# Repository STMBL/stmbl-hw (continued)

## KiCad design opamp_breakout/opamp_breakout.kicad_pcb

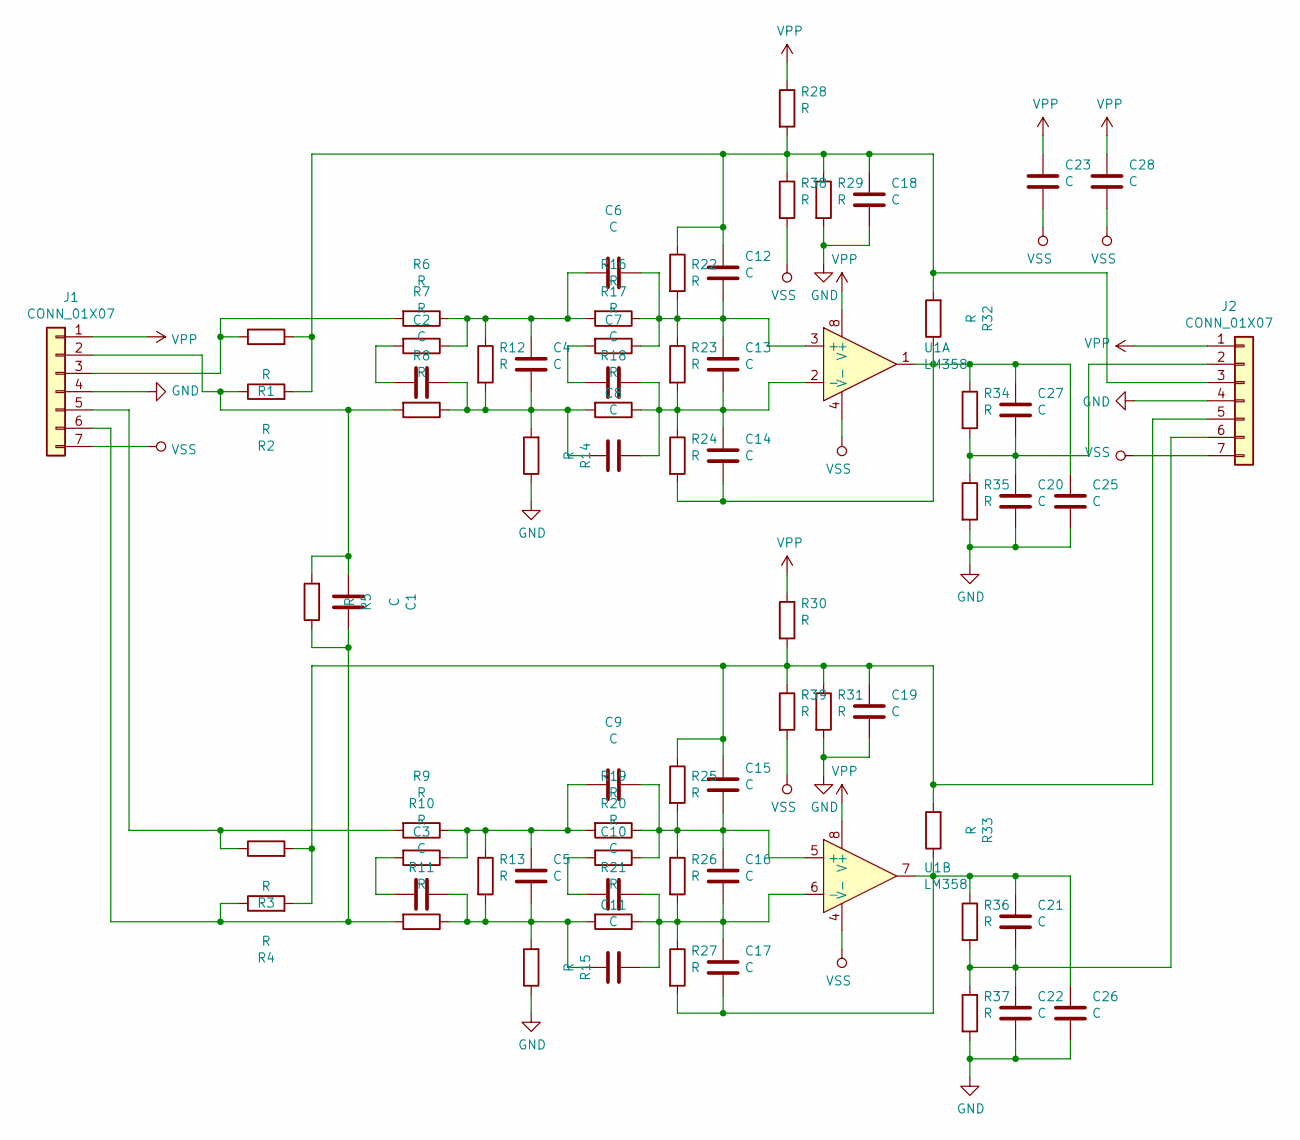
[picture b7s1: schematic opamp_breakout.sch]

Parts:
C1, C2, C3, C4, C5, C6, C7, C8, C9, C10, C11, C12, C13, C14, C15, C16, C17, C18, C19, C20, C21, C22, C23, C25, C26, C27, C28: C; 0603_jumper
J1, J2: CONN_01X07; Pin_Header_RM2.54_1x7_UP
R1, R2, R3, R4, R5, R6, R7, R8, R9, R10, R11, R12, R13, R14, R15, R16, R17, R18, R19, R20, R21, R22, R23, R24, R25, R26, R27, R28, R29, R30, R31, R32, R33, R34, R35, R36, R37, R38, R39: R; 0603_jumper
U1: LM358; SOIC-8-N

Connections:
GND: C18.2, C19.2, C20.2, C22.2, C25.2, C26.2, J1.4, J2.4, R14.1, R15.1, R29.2, R31.2, R35.2, R37.2
unnamed: C1.1, J1.6, R4.1, R5.1, R11.2
unnamed: C1.2, J1.2, R2.1, R5.2, R8.2
unnamed: C2.1, C4.2, C8.2, R8.1, R12.2, R14.2, R18.2
unnamed: C2.2, R7.2
unnamed: C3.2, R10.2
unnamed: C4.1, C6.2, R6.1, R7.1, R12.1, R16.2
unnamed: C5.1, C9.2, R9.1, R10.1, R13.1, R19.2
unnamed: C7.2, R17.2
unnamed: C10.1, C11.1, C16.2, C17.1, R21.1, R26.2, R27.1, U1.6 (-)
unnamed: C10.2, R20.2
unnamed: C3.1, C5.2, C11.2, R11.1, R13.2, R15.2, R21.2
unnamed: C12.1, C18.1, J2.3, R1.2, R2.2, R22.1, R28.2, R29.1, R32.2, R38.1
unnamed: C6.1, C12.2, C13.1, R16.1, R17.1, R22.2, R23.1, U1.3 (+)
unnamed: C7.1, C8.1, C13.2, C14.1, R18.1, R23.2, R24.1, U1.2 (-)
unnamed: C14.2, C25.1, C27.1, R24.2, R32.1, R34.1, U1.1
unnamed: C15.1, C19.1, J2.5, R3.2, R4.2, R25.1, R30.2, R31.1, R33.2, R39.1
unnamed: C9.1, C15.2, C16.1, R19.1, R20.1, R25.2, R26.1, U1.5 (+)
unnamed: C17.2, C21.1, C26.1, R27.2, R33.1, R36.1, U1.7
unnamed: C20.1, C27.2, J2.2, R34.2, R35.1
unnamed: C21.2, C22.1, J2.6, R36.2, R37.1
unnamed: J1.3, R1.1, R6.2
unnamed: J1.5, R3.1, R9.2
VPP: C23.1, C28.1, J1.1, J2.1, R28.1, R30.1, U1.8 (V+)
VSS: C23.2, C28.2, J1.7, J2.7, R38.2, R39.2, U1.4 (V-)

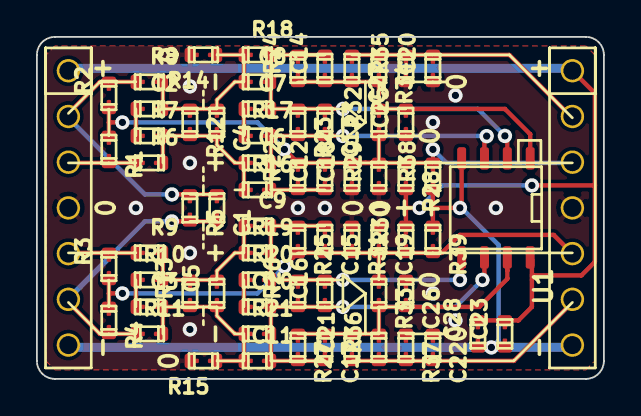
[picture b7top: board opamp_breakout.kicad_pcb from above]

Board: 2 copper layers, 31.5 x 19.0 mm, 69 parts (0 on the bottom side), 25 nets.

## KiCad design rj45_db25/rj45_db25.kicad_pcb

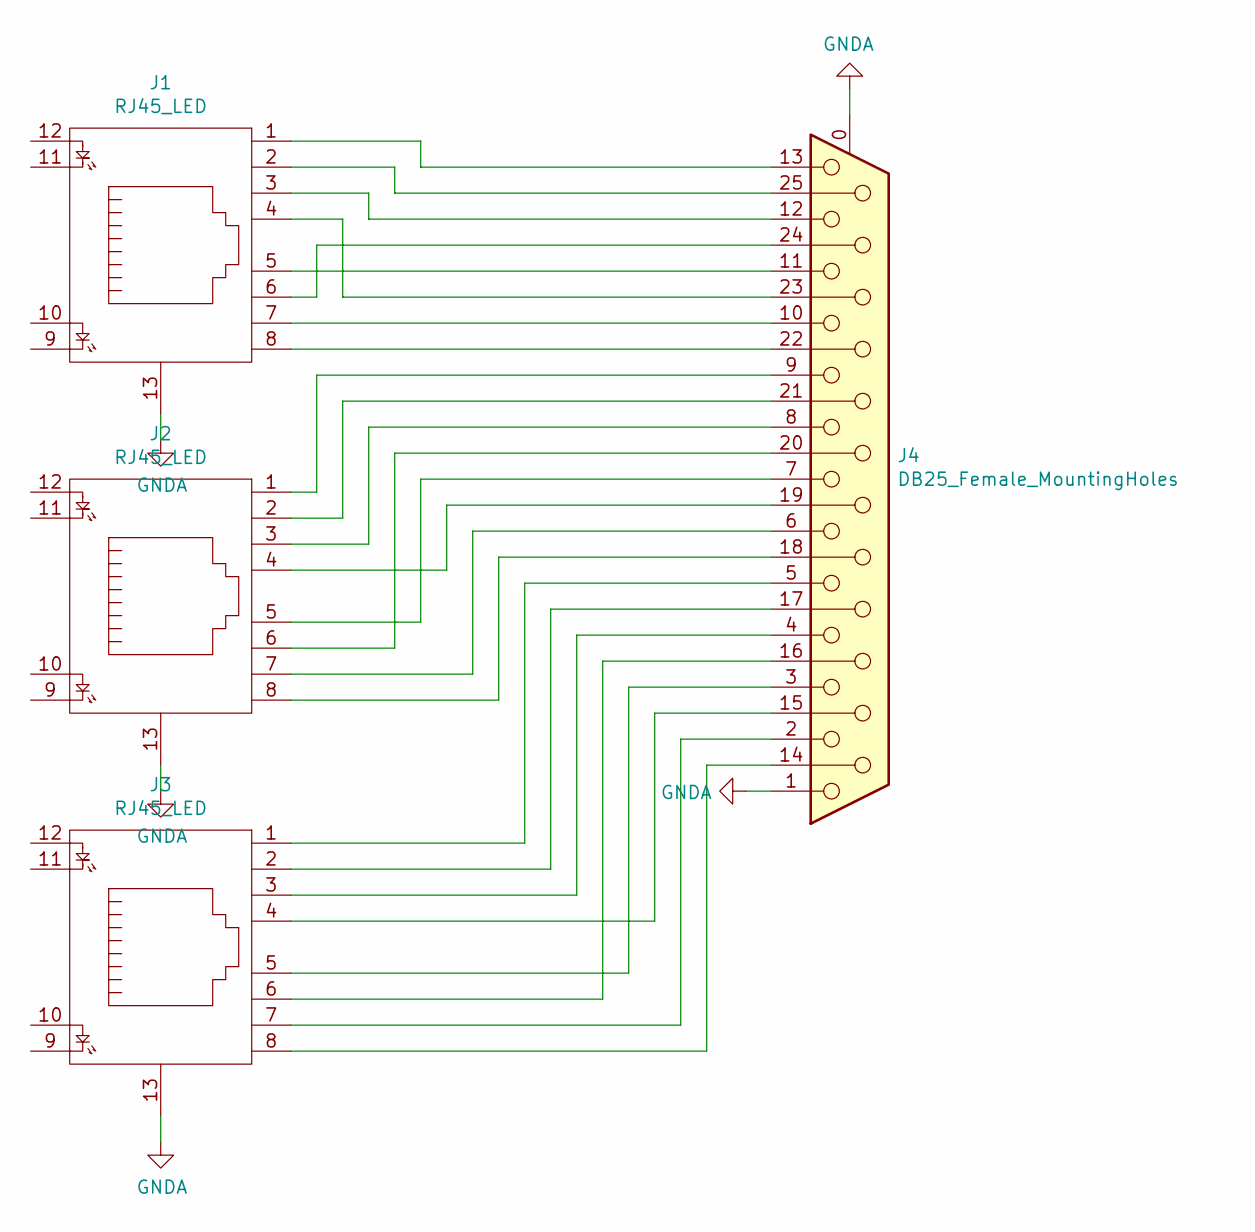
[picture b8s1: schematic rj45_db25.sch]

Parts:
J1, J2, J3: RJ45_LED
J4: DB25_Female_MountingHoles; DSUB-25_Female_Horizontal_P2.77x2.84mm_EdgePinOffset4.94mm_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

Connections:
GNDA: J1.13, J2.13, J3.13, J4.0 (PAD), J4.1
unnamed: J1.1, J4.13
unnamed: J1.2, J4.25
unnamed: J1.3, J4.12
unnamed: J1.4, J4.23
unnamed: J1.5, J4.11
unnamed: J1.6, J4.24
unnamed: J1.7, J4.10
unnamed: J1.8, J4.22
unnamed: J2.1, J4.9
unnamed: J2.2, J4.21
unnamed: J2.3, J4.8
unnamed: J2.4, J4.19
unnamed: J2.5, J4.7
unnamed: J2.6, J4.20
unnamed: J2.7, J4.6
unnamed: J2.8, J4.18
unnamed: J3.1, J4.5
unnamed: J3.2, J4.17
unnamed: J3.3, J4.4
unnamed: J3.4, J4.15
unnamed: J3.5, J4.3
unnamed: J3.6, J4.16
unnamed: J3.7, J4.2
unnamed: J3.8, J4.14

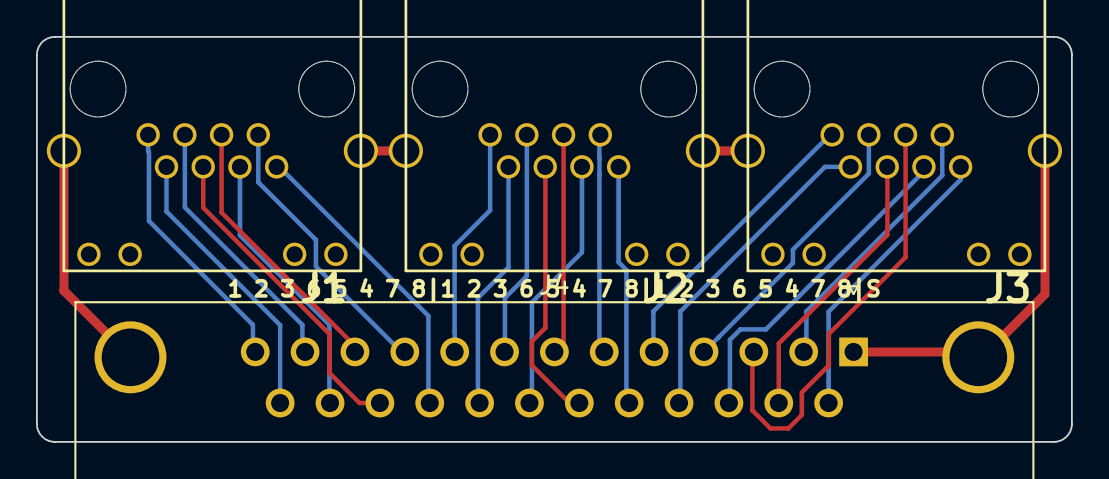
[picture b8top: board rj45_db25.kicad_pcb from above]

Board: 2 copper layers, 57.5 x 22.5 mm, 4 parts (0 on the bottom side), 25 nets.

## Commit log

2020-01-21 hx711
2020-01-22 rs485
2020-01-22 move
2020-01-27 parts
2020-01-28 jlc export
2020-01-28 rot fix
2020-04-13 Finish routing of the PFC PCB
2020-04-15 add component values and mounting hole
2020-05-05 fix new file format
2020-05-06 footprint remap
2020-05-07 sort place
2020-05-08 lcsc part mapping
2020-05-11 fix diode rotation
